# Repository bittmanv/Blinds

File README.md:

# Blinds
Project covering automated automated blinds with Openhab

Published based on request on Openhab discussion forums

espRoller32 Arduino based sketch 

ShadeEsp32Mini  Kicad project for PCB With MH Mini ESP32 Board 

ShadeEsp32V2 Kicad project for PCB Based on ESP32 Wroom module 

PCBs I have made with my laser engraver with black masked , precision and allign was little bit limiting 

# High level summary

  We have 2 double windows in our kithen/living room. I have bought 2 sun stop blinds and I implemented as part of my home automation to enable privacy on windows coming from street and escpecially on window from south to limit sun which was lights directly to peoples sitting face to window. During summer I use them as aditional temperature and light for room. 
  
  Whole scheduling is based on openhab rules. 

 # Material summary
 JGA25-12V chinese motors with encoder, appox 25rpm  is fine 

 DRV8872  H-Bridge (for each motor) 
 
 Mini360  Buck step down module 
 
 AMS 1117-3.3V regulator 
 
 Some SMD and THT Passive parts according to schematic

 Optionally 
 
 Omron G2MB 5V SSR Relay - we have small 220V led bulb as over window, which is also controlled by automation

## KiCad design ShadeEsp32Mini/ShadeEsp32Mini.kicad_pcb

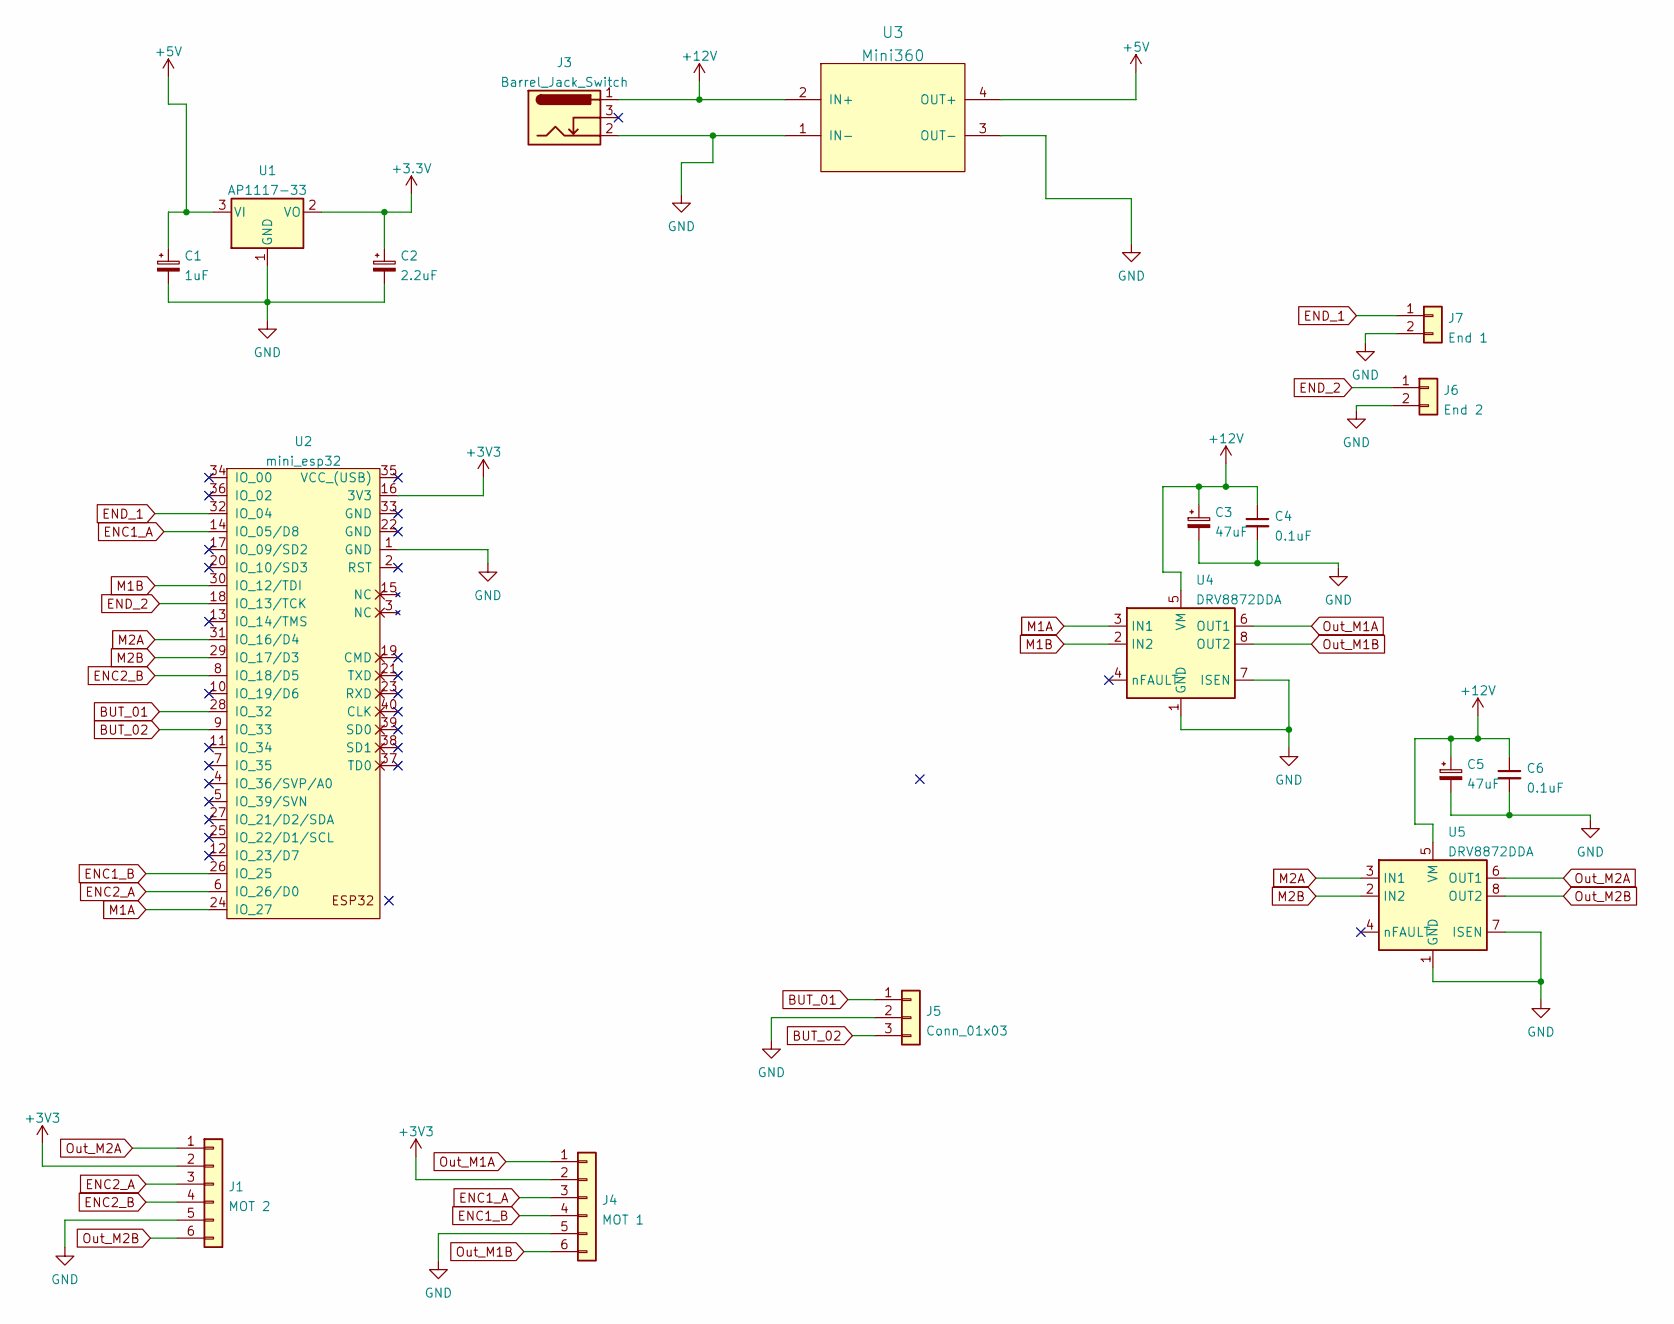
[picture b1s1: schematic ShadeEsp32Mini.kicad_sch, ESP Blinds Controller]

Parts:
C1: 1uF; CP_Radial_D6.3mm_P2.50mm
C2: 2.2uF; CP_Radial_D6.3mm_P2.50mm
C3, C5: 47uF; CP_Radial_D6.3mm_P2.50mm
C4, C6: 0.1uF; C_1206_3216Metric_Pad1.33x1.80mm_HandSolder
J1: MOT 2; JST_PH_S6B-PH-K_1x06_P2.00mm_Horizontal
J3: Barrel_Jack_Switch; BarrelJack_Horizontal
J4: MOT 1; JST_PH_S6B-PH-K_1x06_P2.00mm_Horizontal
J5: Conn_01x03; JST_XH_S3B-XH-A_1x03_P2.50mm_Horizontal
J6: End 2; JST_XH_S2B-XH-A_1x02_P2.50mm_Horizontal
J7: End 1; JST_XH_S2B-XH-A_1x02_P2.50mm_Horizontal
U1: AP1117-33; SOT-223-3_TabPin2
U2: mini_esp32; ESP32_mini
U3: Mini360; Mini360_step-down
U4, U5: DRV8872DDA; Texas_HTSOP-8-1EP_3.9x4.9mm_P1.27mm_EP2.95x4.9mm_Mask2.4x3.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

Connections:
+5V: C1.1, U1.3 (VI), U3.4 (OUT+)
+12V: C3.1, C4.1, C5.1, C6.1, J3.1, U3.2 (IN+), U4.5 (VM), U5.5 (VM)
BUT_01: J5.1, U2.28 (IO_32)
BUT_02: J5.3, U2.9 (IO_33)
ENC1_A: J4.3, U2.14 (IO_05/D8)
ENC1_B: J4.4, U2.26 (IO_25)
ENC2_A: J1.3, U2.6 (IO_26/D0)
ENC2_B: J1.4, U2.8 (IO_18/D5)
END_1: J7.1, U2.32 (IO_04)
END_2: J6.1, U2.18 (IO_13/TCK)
GND: C1.2, C2.2, C3.2, C4.2, C5.2, C6.2, J1.5, J3.2, J4.5, J5.2, J6.2, J7.2, U1.1 (GND), U2.1 (GND), U3.1 (IN-), U3.3 (OUT-), U4.1 (GND), U4.7 (ISEN), U4.9 (GND), U5.1 (GND), U5.7 (ISEN), U5.9 (GND)
M1A: U2.24 (IO_27), U4.3 (IN1)
M1B: U2.30 (IO_12/TDI), U4.2 (IN2)
M2A: U2.31 (IO_16/D4), U5.3 (IN1)
M2B: U2.29 (IO_17/D3), U5.2 (IN2)
Out_M1A: J4.1, U4.6 (OUT1)
Out_M1B: J4.6, U4.8 (OUT2)
Out_M2A: J1.1, U5.6 (OUT1)
Out_M2B: J1.6, U5.8 (OUT2)

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
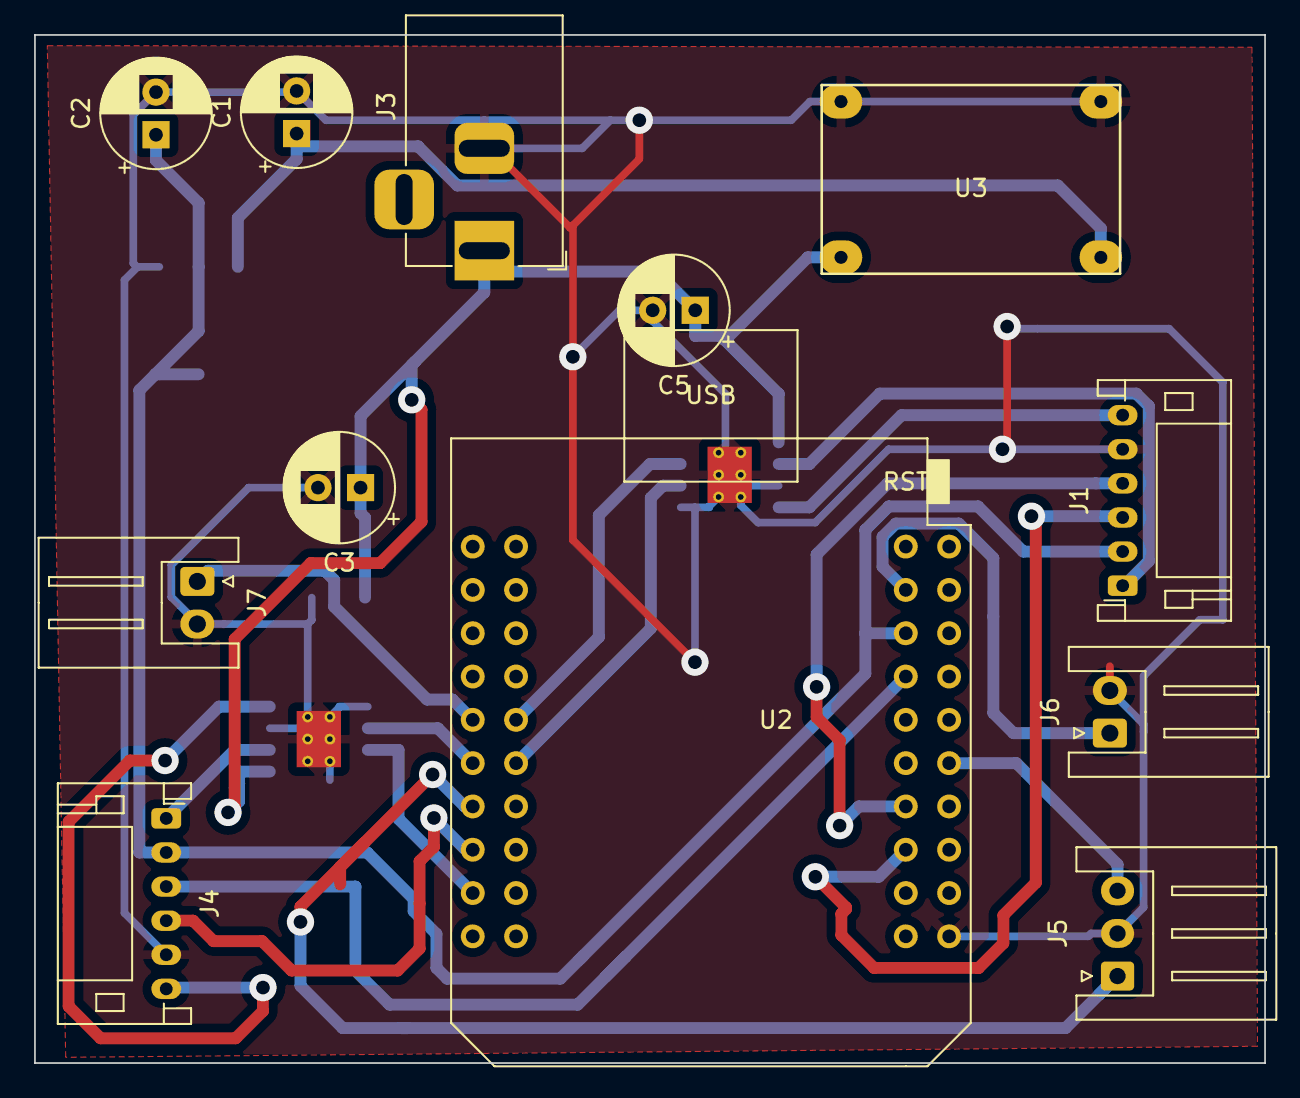
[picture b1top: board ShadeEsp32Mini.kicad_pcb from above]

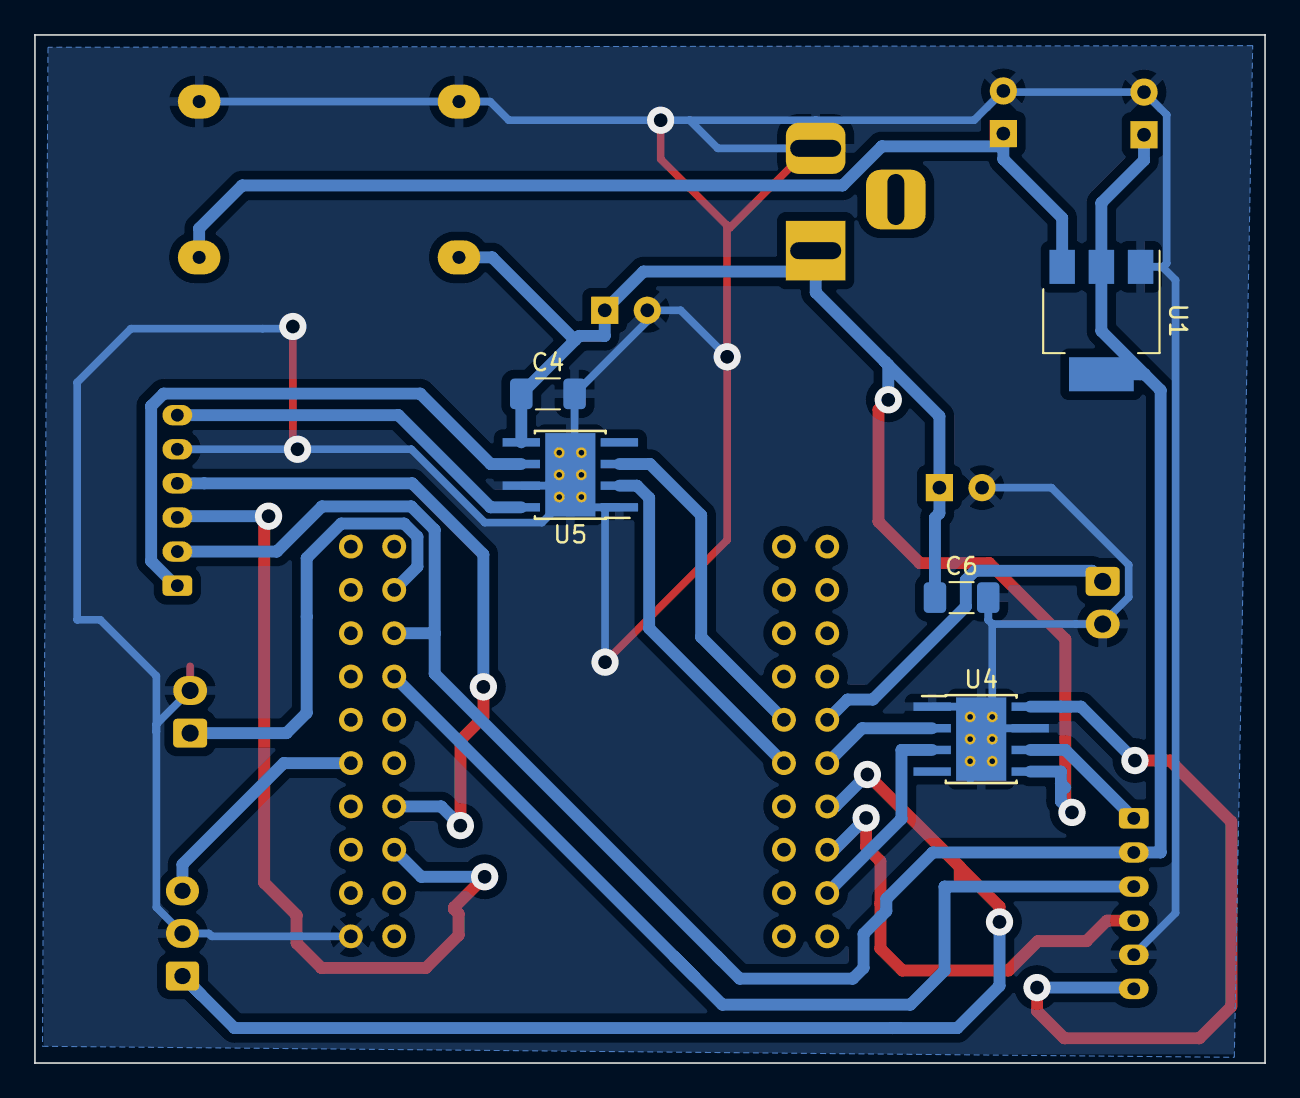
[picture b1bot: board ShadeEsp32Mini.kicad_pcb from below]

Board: 2 copper layers, 72.2 x 60.3 mm, 17 parts (5 on the bottom side), 20 nets.

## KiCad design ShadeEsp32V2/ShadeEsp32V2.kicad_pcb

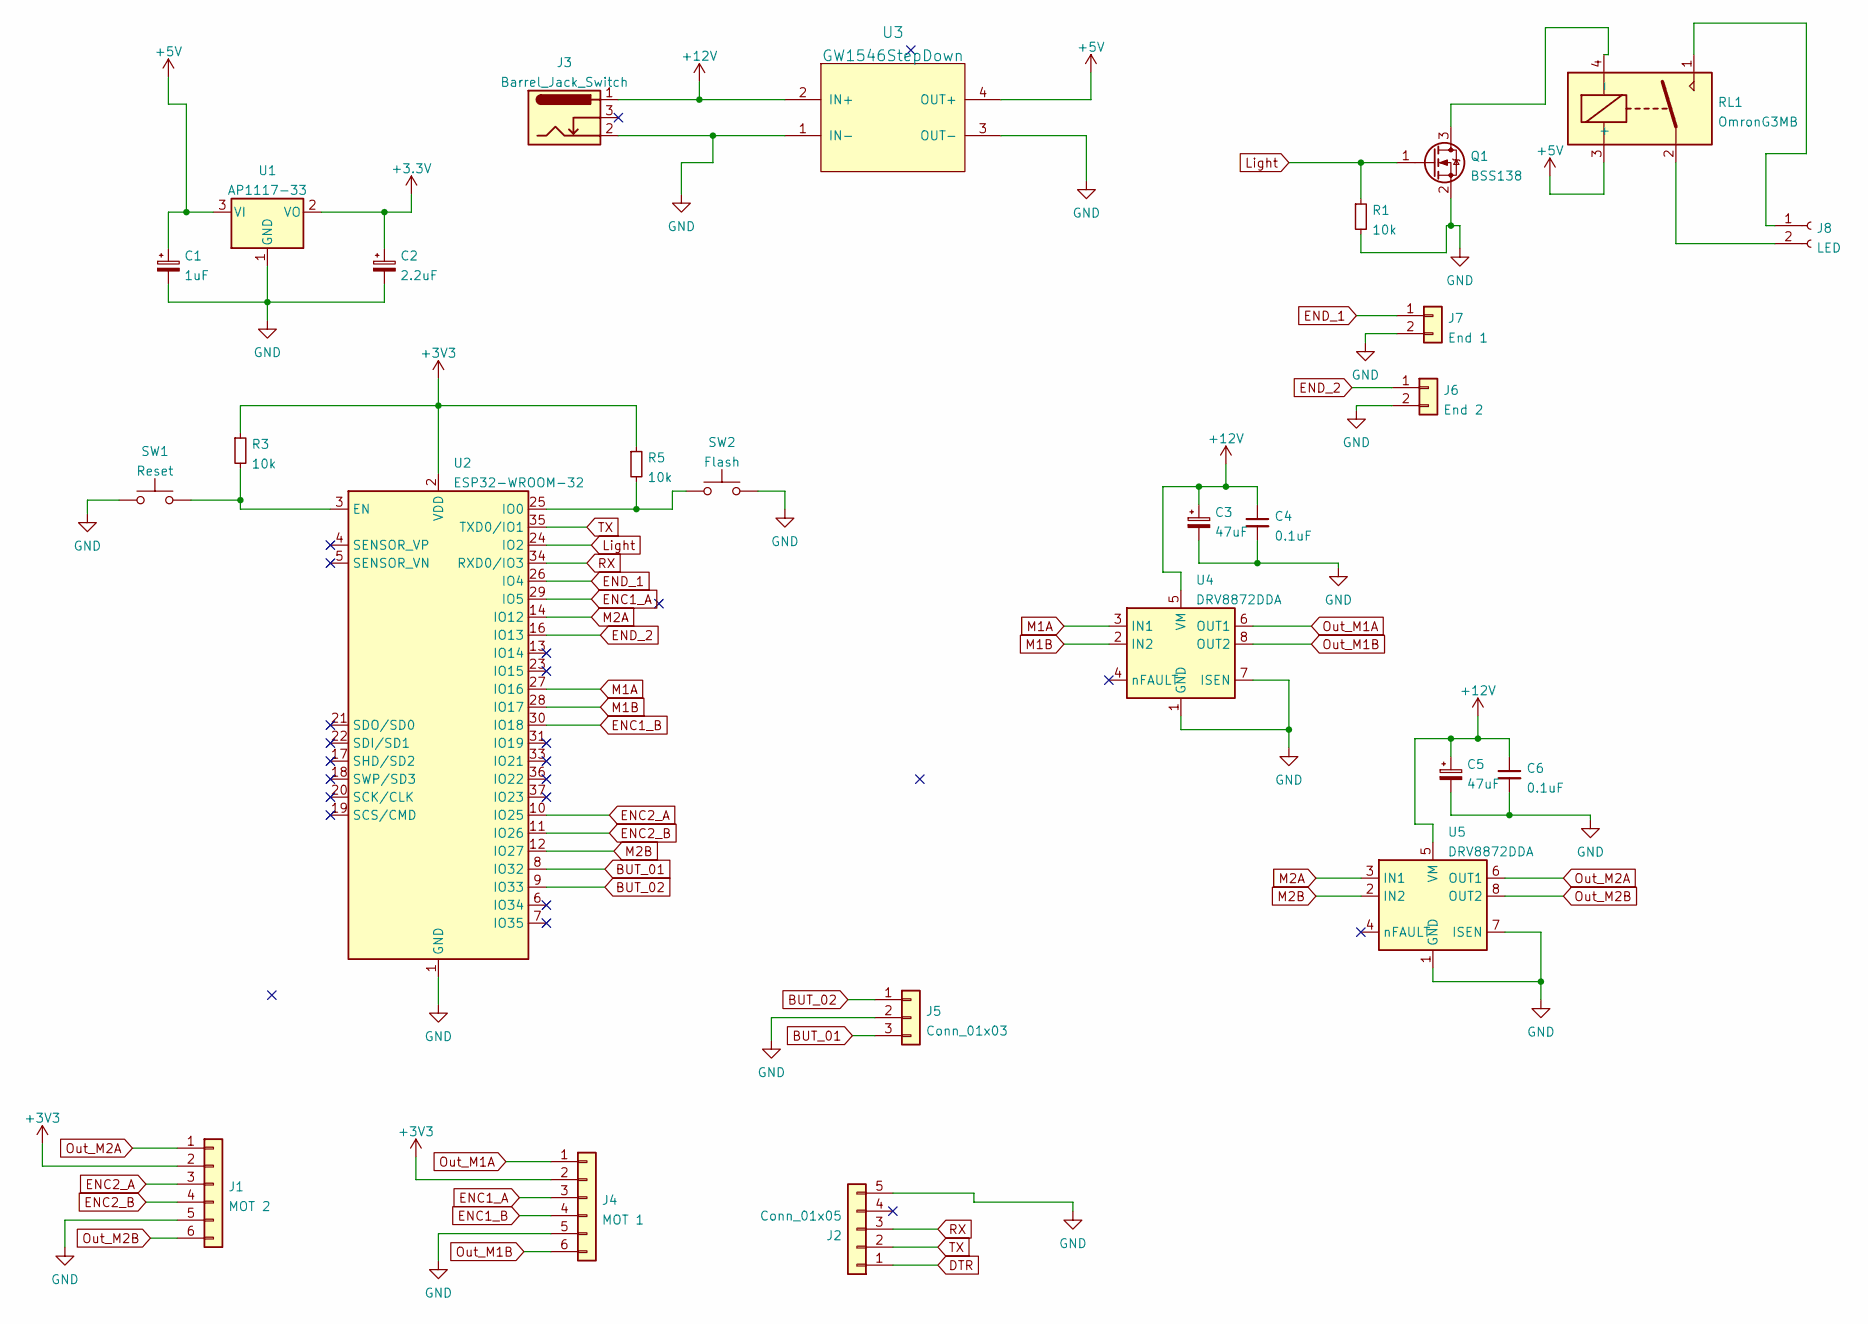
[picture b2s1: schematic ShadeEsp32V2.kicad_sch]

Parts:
C1: 1uF; CP_Elec_5x4.4
C2: 2.2uF; CP_Elec_6.3x4.9
C3, C5: 47uF; CP_Elec_5x5.3
C4, C6: 0.1uF; C_1206_3216Metric_Pad1.33x1.80mm_HandSolder
J1: MOT 2; JST_PH_S6B-PH-K_1x06_P2.00mm_Horizontal
J2: Conn_01x05; JST_PH_S5B-PH-SM4-TB_1x05-1MP_P2.00mm_Horizontal
J3: Barrel_Jack_Switch; BarrelJack_Horizontal
J4: MOT 1; JST_PH_S6B-PH-K_1x06_P2.00mm_Horizontal
J5: Conn_01x03; JST_PH_S3B-PH-SM4-TB_1x03-1MP_P2.00mm_Horizontal
J6: End 2; JST_PH_S2B-PH-SM4-TB_1x02-1MP_P2.00mm_Horizontal
J7: End 1; JST_PH_S2B-PH-SM4-TB_1x02-1MP_P2.00mm_Horizontal
J8: LED; mkds_1,5-2
Q1: BSS138; SOT-23
R1, R3, R5: 10k; R_1206_3216Metric_Pad1.30x1.75mm_HandSolder
RL1: OmronG3MB; RELAY_G3MB202PDC12
SW1: Reset; SW_Push_1P1T_NO_6x6mm_H9.5mm
SW2: Flash; SW_Push_1P1T_NO_6x6mm_H9.5mm
U1: AP1117-33; SOT-223-3_TabPin2
U2: ESP32-WROOM-32
U3: GW1546StepDown; Mini360_step-down
U4, U5: DRV8872DDA; Texas_HTSOP-8-1EP_3.9x4.9mm_P1.27mm_EP2.95x4.9mm_Mask2.4x3.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

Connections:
+5V: C1.1, RL1.3 (+), U1.3 (VI), U3.4 (OUT+)
+12V: C3.1, C4.1, C5.1, C6.1, J3.1, U3.2 (IN+), U4.5 (VM), U5.5 (VM)
BUT_01: J5.3, U2.8 (IO32)
BUT_02: J5.1, U2.9 (IO33)
DTR: J2.1
ENC1_A: J4.3, U2.29 (IO5)
ENC1_B: J4.4, U2.30 (IO18)
ENC2_A: J1.3, U2.10 (IO25)
ENC2_B: J1.4, U2.11 (IO26)
END_1: J7.1, U2.26 (IO4)
END_2: J6.1, U2.16 (IO13)
GND: C1.2, C2.2, C3.2, C4.2, C5.2, C6.2, J1.5, J2.5, J3.2, J4.5, J5.2, J6.2, J7.2, Q1.2 (S), R1.2, SW1.1, SW2.2, U1.1 (GND), U2.1 (GND), U2.15 (GND), U2.38 (GND), U2.39 (GND), U3.1 (IN-), U3.3 (OUT-), U4.1 (GND), U4.7 (ISEN), U4.9 (GND), U5.1 (GND), U5.7 (ISEN), U5.9 (GND)
Light: Q1.1 (G), R1.1, U2.24 (IO2)
M1A: U2.27 (IO16), U4.3 (IN1)
M1B: U2.28 (IO17), U4.2 (IN2)
M2A: U2.14 (IO12), U5.3 (IN1)
M2B: U2.12 (IO27), U5.2 (IN2)
unnamed: J8.1, RL1.1
unnamed: J8.2, RL1.2
unnamed: Q1.3 (D), RL1.4 (-)
unnamed: R3.2, SW1.2, U2.3 (EN)
unnamed: R5.2, SW2.1, U2.25 (IO0)
Out_M1A: J4.1, U4.6 (OUT1)
Out_M1B: J4.6, U4.8 (OUT2)
Out_M2A: J1.1, U5.6 (OUT1)
Out_M2B: J1.6, U5.8 (OUT2)
RX: J2.3, U2.34 (RXD0/IO3)
TX: J2.2, U2.35 (TXD0/IO1)

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
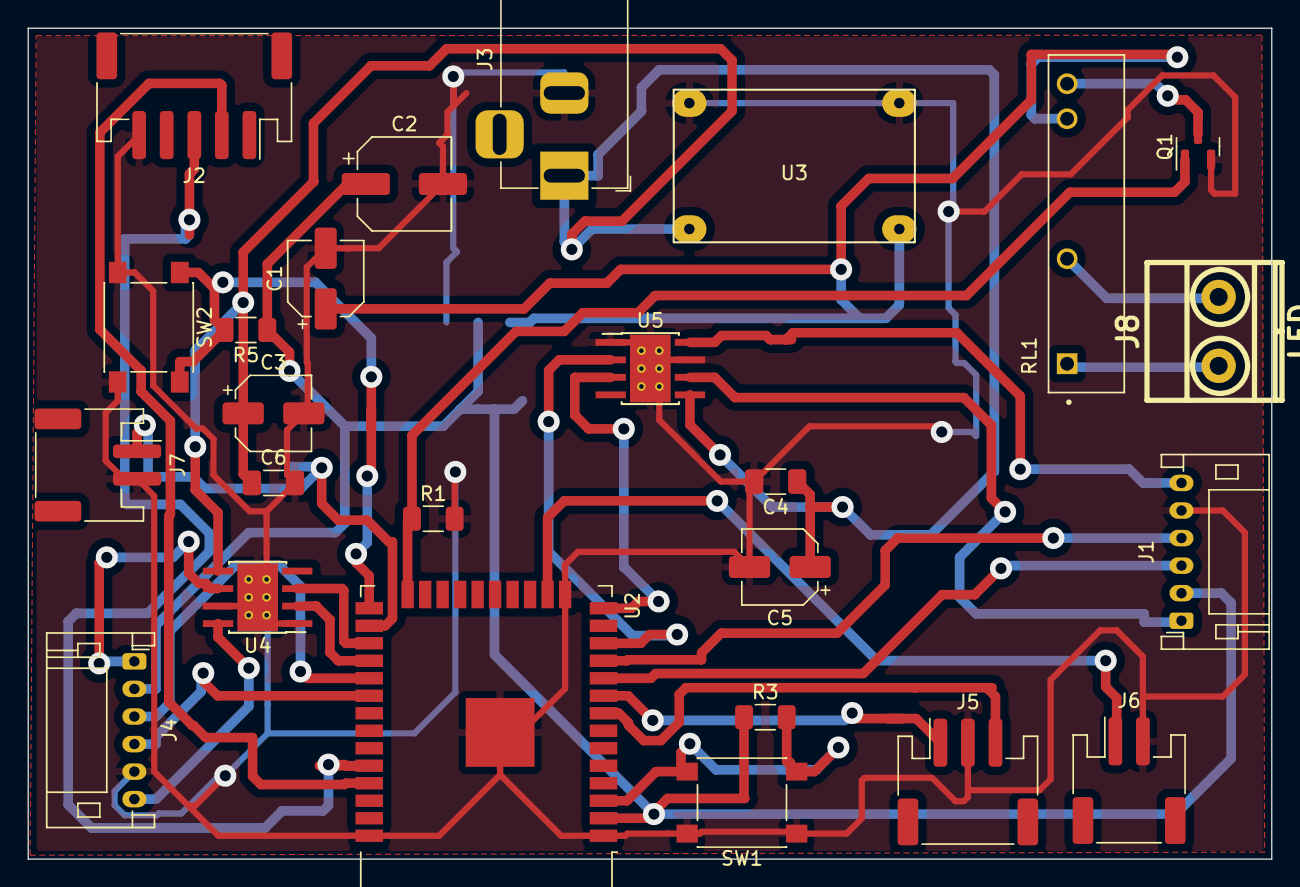
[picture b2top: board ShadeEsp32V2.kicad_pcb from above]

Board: 2 copper layers, 90.3 x 60.3 mm, 26 parts (1 on the bottom side), 28 nets.

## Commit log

2023-11-07 Initial data consolidation for publishing
